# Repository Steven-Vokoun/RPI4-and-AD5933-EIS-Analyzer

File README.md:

# RPI4 and AD5933 EIS Analyzer
Overview:
- Mostly functioning but needs improvements.
- Libraries for AD5933 and MUX's working at this time.
- GUI utilizes custom tkinter.
- Fitting utilized "Impedance" python library (planning to update for robustness)
- Automatic gain switching methods implemented, but has bugs

Improvements I need to make in the future:
- Implementation of the internal 5x switchable gains
- Shift screen off to the left hand side of the enclosure, so then the power supply can be placed right next to the analog board.  Also put filtering on the i2c lines.
- Configuration of 3 electrode switching with a double pole relay instead to completely get it out of the circuit
- Have an external calibration board to account for lead inductance and capacitance
- Add a warning for when the output is hitting supply rails

Future Goals:
- Switch off of a RPI, to a lower level board for lower power consumption
- Shrink the device
- Make my own battery management board

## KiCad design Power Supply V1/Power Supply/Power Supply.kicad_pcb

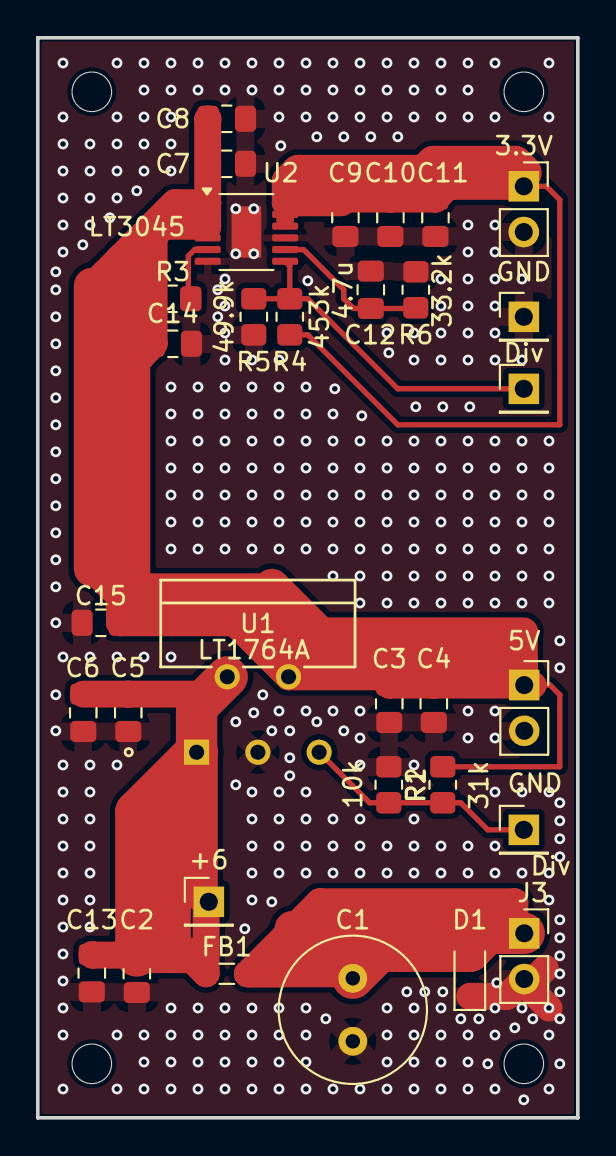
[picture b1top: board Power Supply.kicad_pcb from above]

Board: 2 copper layers, 30.0 x 60.0 mm, 36 parts (0 on the bottom side), 9 nets.

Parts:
3.3V, 5V: Conn_01x02_Pin; PinSocket_1x02_P2.54mm_Vertical
+6: Conn_01x01_Pin; PinHeader_1x01_P2.54mm_Vertical
C1: 100u; C_Radial_D8.0mm_H11.5mm_P3.50mm
C2, C3, C8, C13: 22u; C_0805_2012Metric_Pad1.18x1.45mm_HandSolder
C4, C6, C7, C11: .1u; C_0805_2012Metric_Pad1.18x1.45mm_HandSolder
C5, C9, C10, C14, C15: 10u; C_0805_2012Metric_Pad1.18x1.45mm_HandSolder
C12: 4.7u; C_0805_2012Metric_Pad1.18x1.45mm_HandSolder
D1: CDSOD323-To8; D_SOD-323_HandSoldering
Div: Conn_01x01_Pin; PinHeader_1x01_P2.54mm_Vertical
Div#2: Conn_01x01_Pin; PinHeader_1x01_P2.54mm_Vertical
FB1: Ferrite; L_0805_2012Metric_Pad1.05x1.20mm_HandSolder
GND: Conn_01x01_Pin; PinHeader_1x01_P2.54mm_Vertical
H1, H2, H3, H4: MountingHole; MountingHole_2.2mm_M2
J3: Conn_01x02_Pin; PinSocket_1x02_P2.54mm_Vertical
R1: 31k; R_0805_2012Metric_Pad1.20x1.40mm_HandSolder
R2: 10k; R_0805_2012Metric_Pad1.20x1.40mm_HandSolder
R3: 200k; R_0805_2012Metric_Pad1.20x1.40mm_HandSolder
R4: 453k; R_0805_2012Metric_Pad1.20x1.40mm_HandSolder
R5: 49.9k; R_0805_2012Metric_Pad1.20x1.40mm_HandSolder
R6: 33.2k; R_0805_2012Metric_Pad1.20x1.40mm_HandSolder
U1: LT1764A; TO220-5_T_LIT
U2: LT3045; MSOP-12-1EP_3x4mm_P0.65mm_EP1.65x2.85mm

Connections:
+3.3V: 3.3V.1, C9.1, C10.1, C11.1, R4.1, U2.10 (OUTS), U2.11 (OUT), U2.12 (OUT)
+5V: 5V.1, C3.1, C4.1, C7.1, C8.1, C14.1, C15.1, R1.1, R3.1, U1.4 (OUT), U2.1 (IN), U2.2 (IN), U2.3 (IN), U2.4 (EN/UV)
+6V: +6.1, C2.1, C5.1, C6.1, C13.1, FB1.2, U1.1 (*SHDN), U1.2 (IN)
/Div_1: Div.1, R1.2, R2.1, U1.5 (SENSE/ADJ)
/Div_2: Div#2.1, R4.2, R5.1, U2.7 (PGFB)
GND: 3.3V.2, 5V.2, C1.2, C2.2, C3.2, C4.2, C5.2, C6.2, C7.2, C8.2, C9.2, C10.2, C11.2, C12.2, C13.2, C14.2, C15.2, D1.1 (A1), GND.1, J3.2, R2.2, R5.2, R6.2, U1.3 (GND), U2.6 (ILIM), U2.9 (GND), U2.13 (GND)
unnamed: R3.2, U2.5 (PG)
unnamed: C12.1, R6.1, U2.8 (SET)
VCC: C1.1, D1.2 (A2), FB1.1, J3.1

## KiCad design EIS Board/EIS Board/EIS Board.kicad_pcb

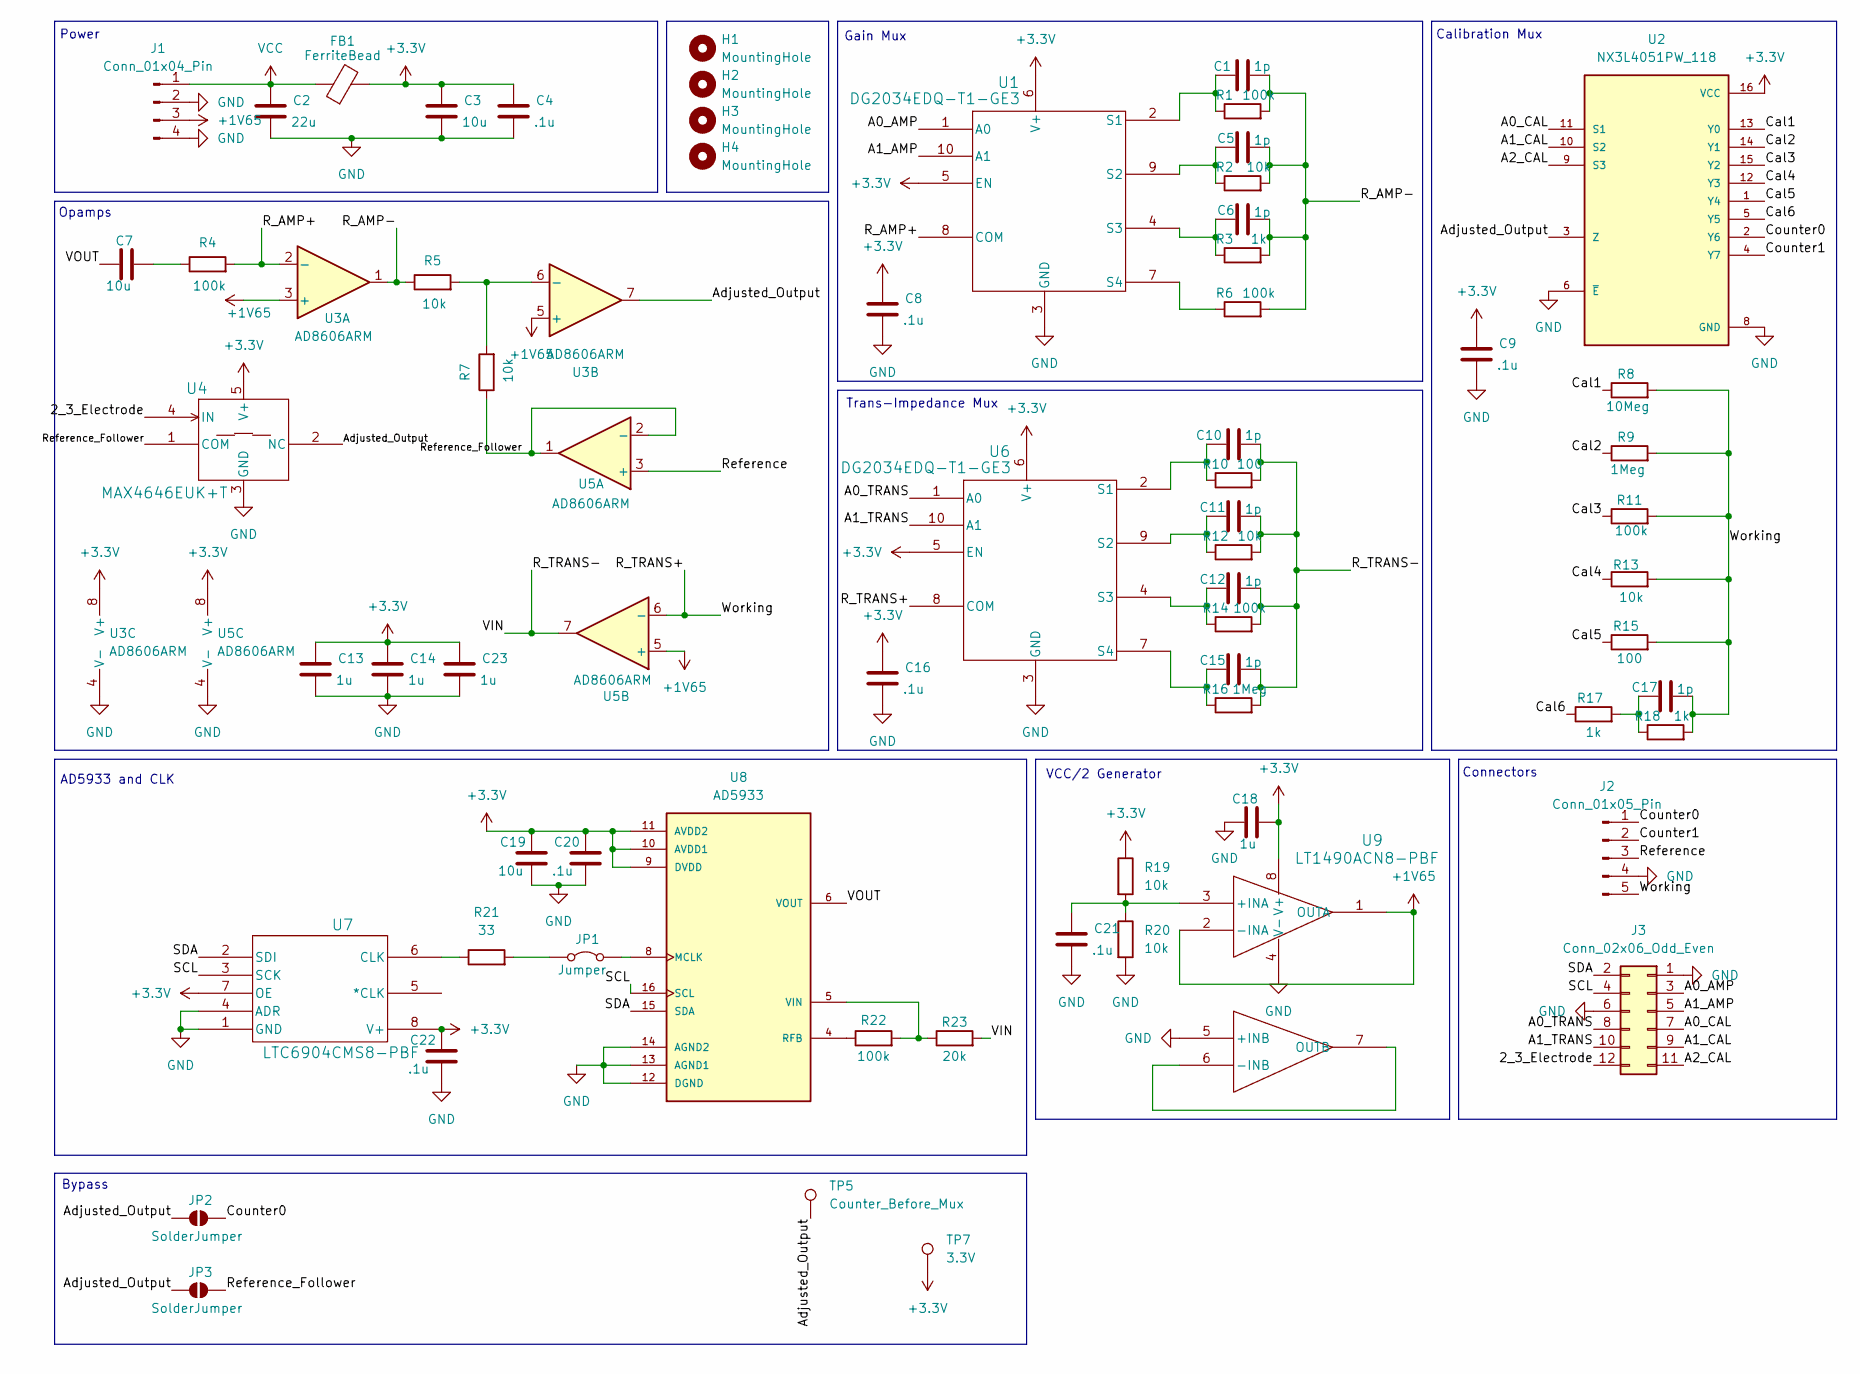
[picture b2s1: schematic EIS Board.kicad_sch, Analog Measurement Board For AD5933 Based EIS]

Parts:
C1, C5, C6, C10, C11, C12, C15, C17: 1p; C_0805_2012Metric_Pad1.18x1.45mm_HandSolder
C2: 22u; C_0805_2012Metric_Pad1.18x1.45mm_HandSolder
C3, C7, C19: 10u; C_0805_2012Metric_Pad1.18x1.45mm_HandSolder
C4, C8, C9, C16, C20, C21, C22: .1u; C_0805_2012Metric_Pad1.18x1.45mm_HandSolder
C13, C14, C18, C23: 1u; C_0805_2012Metric_Pad1.18x1.45mm_HandSolder
FB1: FerriteBead; L_0805_2012Metric_Pad1.05x1.20mm_HandSolder
H1, H2, H3, H4: MountingHole; MountingHole_2.2mm_M2
J1: Conn_01x04_Pin; PinHeader_1x04_P2.54mm_Vertical
J2: Conn_01x05_Pin; PinHeader_1x05_P2.54mm_Vertical
J3: Conn_02x06_Odd_Even; PinHeader_2x06_P2.54mm_Vertical
JP1: Jumper; TestPoint_2Pads_Pitch2.54mm_Drill0.8mm
JP2, JP3: SolderJumper; SolderJumper-2_P1.3mm_Open_RoundedPad1.0x1.5mm
R1, R4, R6, R11, R14, R22: 100k; R_0805_2012Metric_Pad1.20x1.40mm_HandSolder
R2, R5, R7, R12, R13, R19, R20: 10k; R_0805_2012Metric_Pad1.20x1.40mm_HandSolder
R3, R17, R18: 1k; R_0805_2012Metric_Pad1.20x1.40mm_HandSolder
R8: 10Meg; R_0805_2012Metric_Pad1.20x1.40mm_HandSolder
R9, R16: 1Meg; R_0805_2012Metric_Pad1.20x1.40mm_HandSolder
R10, R15: 100; R_0805_2012Metric_Pad1.20x1.40mm_HandSolder
R21: 33; R_0805_2012Metric_Pad1.20x1.40mm_HandSolder
R23: 20k; R_0805_2012Metric_Pad1.20x1.40mm_HandSolder
TP5: Counter_Before_Mux; TestPoint_Loop_D1.80mm_Drill1.0mm_Beaded
TP7: 3.3V; TestPoint_Loop_D1.80mm_Drill1.0mm_Beaded
U1, U6: DG2034EDQ-T1-GE3; SMT_EDQ-T1-GE3_VIS
U2: NX3L4051PW_118; SOP65P640X110-16N; PARTREV 5, 3 July 2012
U3, U5: AD8606ARM; MSOP-8_3x3mm_P0.65mm
U4: MAX4646EUK+T; 21-0057F_MXM
U7: LTC6904CMS8-PBF; MSOP-8_MS_LIT
U8: AD5933; SOP65P780X200-16N; PARTREV F
U9: LT1490ACN8-PBF; PDIP-8_N_LIT

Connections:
+1V65: J1.3, U3.3 (+), U3.5 (+), U5.5 (+), U9.1 (OUTA), U9.2 (-INA)
+3.3V: C3.1, C4.1, C8.1, C9.1, C13.1, C14.1, C16.1, C18.2, C19.1, C20.1, C22.1, C23.1, FB1.2, R19.1, TP7.1, U1.5 (EN), U1.6 (V+), U2.16 (VCC), U3.8 (V+), U4.5 (V+), U5.8 (V+), U6.5 (EN), U6.6 (V+), U7.7 (OE), U7.8 (V+), U8.9 (DVDD), U8.10 (AVDD1), U8.11 (AVDD2), U9.8 (V+)
/2_3_Electrode: J3.12, U4.4 (IN)
/A0_AMP: J3.3, U1.1 (A0)
/A0_CAL: J3.7, U2.11 (S1)
/A0_TRANS: J3.8, U6.1 (A0)
/A1_AMP: J3.5, U1.10 (A1)
/A1_CAL: J3.9, U2.10 (S2)
/A1_TRANS: J3.10, U6.10 (A1)
/A2_CAL: J3.11, U2.9 (S3)
/Adjusted_Output: JP2.1 (A), JP3.1 (A), TP5.1, U2.3 (Z), U3.7, U4.2 (NC)
/Cal1: R8.1, U2.13 (Y0)
/Cal2: R9.1, U2.14 (Y1)
/Cal3: R11.1, U2.15 (Y2)
/Cal4: R13.1, U2.12 (Y3)
/Cal5: R15.1, U2.1 (Y4)
/Cal6: R17.1, U2.5 (Y5)
/Counter0: J2.1, JP2.2 (B), U2.2 (Y6)
/Counter1: J2.2, U2.4 (Y7)
/R_AMP+: R4.2, U1.8 (COM), U3.2 (-)
/R_AMP-: C1.2, C5.2, C6.2, R1.2, R2.2, R3.2, R5.1, R6.2, U3.1
/R_TRANS+: C17.2, J2.5, R8.2, R9.2, R11.2, R13.2, R15.2, R18.2, U5.6 (-), U6.8 (COM)
/R_TRANS-: C10.2, C11.2, C12.2, C15.2, R10.2, R12.2, R14.2, R16.2, R23.2, U5.7
/Reference: J2.3, U5.3 (+)
/Reference_Follower: JP3.2 (B), R7.1, U4.1 (COM), U5.1, U5.2 (-)
/SCL: J3.4, U7.3 (SCK), U8.16 (SCL)
/SDA: J3.2, U7.2 (SDI), U8.15 (SDA)
/VOUT: C7.1, U8.6 (VOUT)
GND: C2.2, C3.2, C4.2, C8.2, C9.2, C13.2, C14.2, C16.2, C18.1, C19.2, C20.2, C21.2, C22.2, C23.2, J1.2, J1.4, J2.4, J3.1, J3.6, R20.2, U1.3 (GND), U2.6 (~E), U2.8 (GND), U3.4 (V-), U4.3 (GND), U5.4 (V-), U6.3 (GND), U7.1 (GND), U7.4 (ADR), U8.12 (DGND), U8.13 (AGND1), U8.14 (AGND2), U9.4 (V-), U9.5 (+INB)
unnamed: C7.2, R4.1
unnamed: C17.1, R17.2, R18.1
unnamed: JP1.1 (A), R21.2
unnamed: JP1.2 (B), U8.8 (MCLK)
unnamed: C1.1, R1.1, U1.2 (S1)
unnamed: C5.1, R2.1, U1.9 (S2)
unnamed: C6.1, R3.1, U1.4 (S3)
unnamed: R6.1, U1.7 (S4)
unnamed: R5.2, R7.2, U3.6 (-)
unnamed: C10.1, R10.1, U6.2 (S1)
unnamed: C11.1, R12.1, U6.9 (S2)
unnamed: C12.1, R14.1, U6.4 (S3)
unnamed: C15.1, R16.1, U6.7 (S4)
unnamed: R21.1, U7.6 (CLK)
unnamed: R22.1, U8.4 (RFB)
unnamed: R22.2, R23.1, U8.5 (VIN)
unnamed: C21.1, R19.2, R20.1, U9.3 (+INA)
unnamed: U9.6 (-INB), U9.7 (OUTB)
VCC: C2.1, FB1.1, J1.1

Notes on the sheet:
Opamps
AD5933 and CLK
VCC/2 Generator
Power
Bypass
Gain Mux
Calibration Mux
Trans-Impedance Mux
Connectors

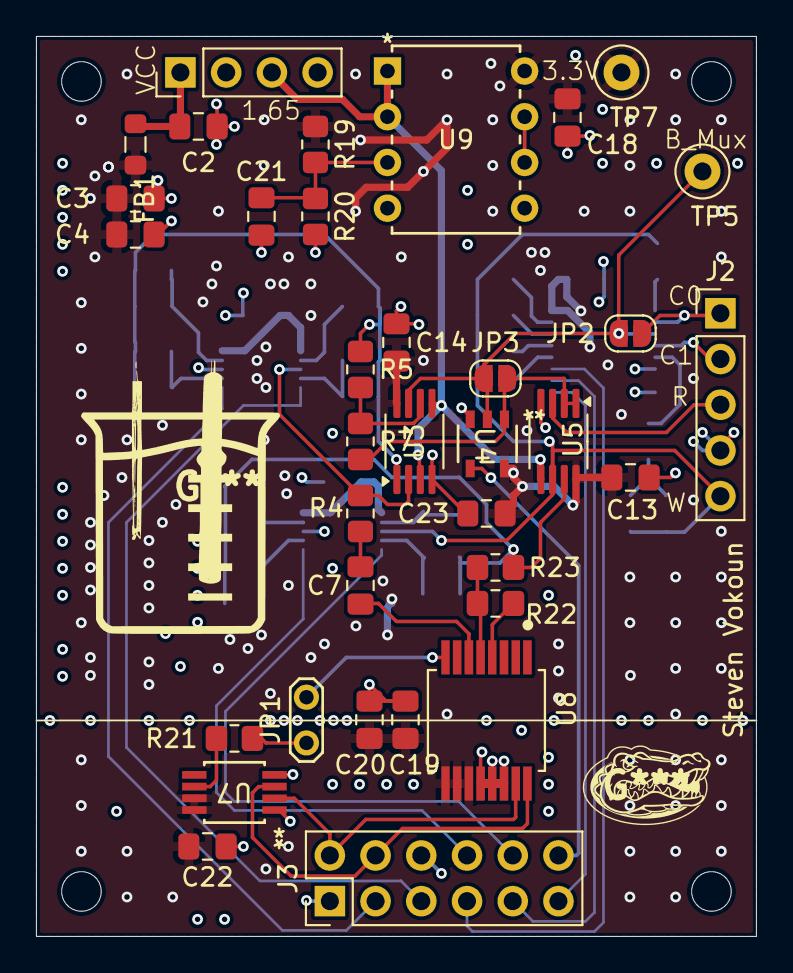
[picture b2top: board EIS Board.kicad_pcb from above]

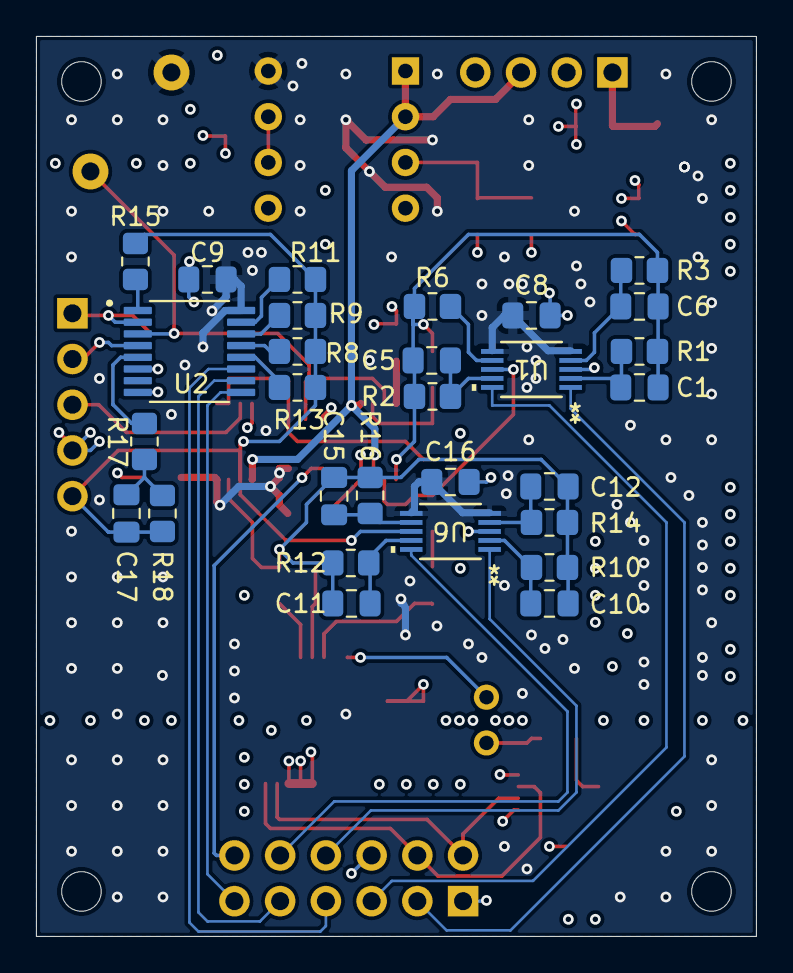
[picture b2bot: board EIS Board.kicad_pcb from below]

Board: 4 copper layers, 40.0 x 50.0 mm, 68 parts (29 on the bottom side), 48 nets.

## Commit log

2024-05-18 Updated the windows and fixed the destructor
2024-05-19 Updated GUI Further. Next task is writing control Library.
2024-05-20 Made Library. Needs Testing.
2024-05-21 Mostly Working Library
2024-05-21 Minor changes to main and library. new test folder.
2024-05-21 Integrated the Library into the GUI. Exporting for testing.
2024-05-21 fixed some errors
2024-05-21 minor fixes.
2024-05-21 minor edit
2024-05-21 Phase Calculation Adjustments. Runs Sucessful Sweep
2024-05-21 Corrections to Phase Calculation
2024-05-22 Added some Debugging for Phase Angle
2024-05-22 Fixing Phase Again
2024-05-22 Added export button integration, notitification window, other bug fixes, enabled prototyping on windows.
2024-05-22 edited export and window size
2024-05-22 edited fit parameters and other minor bugs
2024-05-22 Added close button
2024-05-22 added #!/usr/bin/python3
2024-05-28 Minor Changes
2024-06-14 New Library file
2024-06-14 Minor Update
2024-06-17 Updated it to Custom Tkinter from Tkinter to update the GUI look. Other changes to eis file.
2024-06-18 Changed File Structure
2024-06-19 Minor GUI Changes
2024-07-16 Temporary Test
2024-07-16 Minor errors
2024-07-16 fixed file formatting
2024-07-19 updated file structure
2024-07-20 updates to the MUX methods
2024-07-20 minor fix
2024-07-20 updated MUX Library
2024-07-20 why is this not working
2024-07-21 moved run to eis file instead of library
2024-07-21 added some automatic gain switching and advanced calibration. binary search not yet implemented.
2024-07-21 hardware_components to hardware
2024-07-21 minor
2024-07-21 set output voltage
2024-07-21 edited calibration gain
2024-07-21 number of arguments error
2024-07-21 stupid error input gain fixed
2024-07-21 put back in the test and 3 electrode instead of 2
2024-07-21 what
2024-07-21 I think I figured it out
2024-07-22 stupid mistake
2024-07-22 spelling error
2024-07-22 numerical error
2024-07-22 gramatical error
2024-07-22 int cast
2024-07-22 minor error fix
2024-07-23 fullscreen and select output
2024-07-23 edited size
2024-07-23 Multiple recordings at first datapoint to settle
2024-07-24 gain search algorithm implemented. Not yet tested.
2024-07-24 added calibration class for easier management
2024-07-24 error on import all
2024-07-24 added function for mistake in the search function. Needs improving as this adds overhead.
2024-07-24 converted the auto gain to numpy.
2024-07-24 changes to find impedance from voltage function. needs testing
2024-07-24 conversion to int
2024-07-24 inequality error
2024-07-24 manual override
2024-07-24 changed inequality
2024-07-24 got rid of manual override
2024-07-31 changed phase calculation
2024-07-31 changed to numpy list
2024-07-31 updated default
2024-07-31 minor update why is this not working
2024-07-31 why did it break??
2024-07-31 2 electrode to remove oscillation
2024-07-31 longer settle
2024-07-31 updated averaging
2024-07-31 changes to the auto gain setting
2024-08-01 defaults
2024-08-09 added in the clock generator code
2024-08-09 minor error fix with clk class
2024-08-09 debugging prints
2024-08-09 additional debugging prints
2024-08-09 fixed issue, accidentally using data point 0 instead of the freq in the loop
2024-08-09 changed settling time
2024-08-09 uses internal clock source for frequencies above 10k
2024-10-28 addded schematics
2025-01-27 remove unused CV and Time window classes; add .gitignore for __pycache__
    CV and time window may be implemented later, but will be removed now for time sake.
    git should not track __pycache__, so they will now be ignored and have been removed
2025-01-27 remove unused CV and Time function calls
    The last commit should have also included these changes.
